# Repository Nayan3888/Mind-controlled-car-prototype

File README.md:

# 🧠🚗 Mind-Controlled Car using EEG and IoT

A smart **EEG-based Mind-Controlled Car** system that uses the **NeuroSky MindWave Mobile 2** headset to interpret brainwave signals and control an **ESP32-based robot car** via Bluetooth and HTTP protocols. The system also includes **manual control options** using IR remotes and physical buttons, making it a hybrid multi-input system.

---

## 🚀 Project Overview

This project demonstrates how **EEG (Electroencephalography) signals** can be used to control a robotic vehicle. The headset detects **attention, meditation, and blinks**, which are processed in a **Flutter app** to make real-time movement decisions. The car is then controlled via **Wi-Fi (ESP32 HTTP)** based on the detected mental commands.

---

## 🧩 Features

* 🔗 **Real-time EEG signal processing** from NeuroSky MindWave
* 📱 **Flutter mobile app** for Bluetooth communication and UI
* 🌐 **Wi-Fi-based car control** using ESP32 (HTTP GET/POST)
* 👀 **Blink detection** to trigger left/right movement
* 🧘 **Meditation level** to control reverse
* 🚘 Manual controls via:

  * 📡 IR Remote
  * 🔘 Push buttons on PCB
* 📈 Real-time brainwave data graph (Alpha, Beta, Gamma, etc.)
* 🔌 Power-efficient and multi-mode operation

---

## 🛠️ Hardware Components

| Component               | Description                     |
| ----------------------- | ------------------------------- |
| 🧠 NeuroSky MindWave    | EEG Headset                     |
| 🔲 ESP32-WROOM-32       | Microcontroller with Wi-Fi      |
| 📱 Android Phone        | For Flutter App and EEG parsing |
| 🛞 L298N Motor Driver   | For dual DC motor control       |
| 🔋 Battery              | For powering motors and board   |
| 🔘 IR Receiver + Remote | Manual car control              |
| 📟 16x2 I2C LCD         | (Optional) Display EEG/Status   |
| 💧 Moisture/pH Sensor   | (Optional extension)            |

---

## 📲 Flutter App Features

* Scan and connect to MindWave EEG device (BLE)
* Graphically display EEG metrics (attention, meditation, blink strength)
* Send movement commands to ESP32 via Wi-Fi
* Real-time feedback and alerts

---

## 🔧 How It Works

1. MindWave reads brain signals.
2. Flutter app parses EEG data over Bluetooth using `flutter_blue_plus`.
3. Based on blink or meditation thresholds:

   * Sends commands (e.g., `FORWARD`, `LEFT`, `REVERSE`) to ESP32 via HTTP.
4. ESP32 receives the command and sets motor pins HIGH/LOW using L298N.
5. Manual override is always available via IR or push buttons.

---

## 🧠 EEG Signal Mapping

| EEG Input      | Action Triggered   |
| -------------- | ------------------ |
| Blink Detected | Turn Left or Right |
| Meditation > X | Move in Reverse    |
| Attention > Y  | Move Forward       |
| Idle           | Stop               |

---

## 🔌 Pin Configuration (ESP32)

| Pin      | Description      |
| -------- | ---------------- |
| D5, D18  | Motor A (Front)  |
| D19, D21 | Motor B (Back)   |
| D22      | IR Sensor        |
| D23      | Button 1 (Left)  |
| D25      | Button 2 (Right) |
| 3V3, GND | Power Rails      |

---

## 📁 Project Structure

```
MindControlledCar/
├── flutter_app/           # EEG data processing & UI
├── esp32_code/            # Arduino code for ESP32
├── pcb_design/            # KiCad schematic & PCB layout
├── images/                # System architecture, demo screenshots
└── README.md              # Project documentation
```

---

## 📷 Demo

---

## 📦 Future Enhancements

* Voice commands as secondary control
* Real-time location tracking using GPS
* Web dashboard with EEG logs
* Adaptive control with ML-based pattern recognition

---

## 🤝 Credits

* **Developed by:** Nayan Parekh ,Ved Patel
* **EEG Hardware:** NeuroSky MindWave Mobile 2
* **Embedded System:** ESP32
* **Mobile App:** Flutter

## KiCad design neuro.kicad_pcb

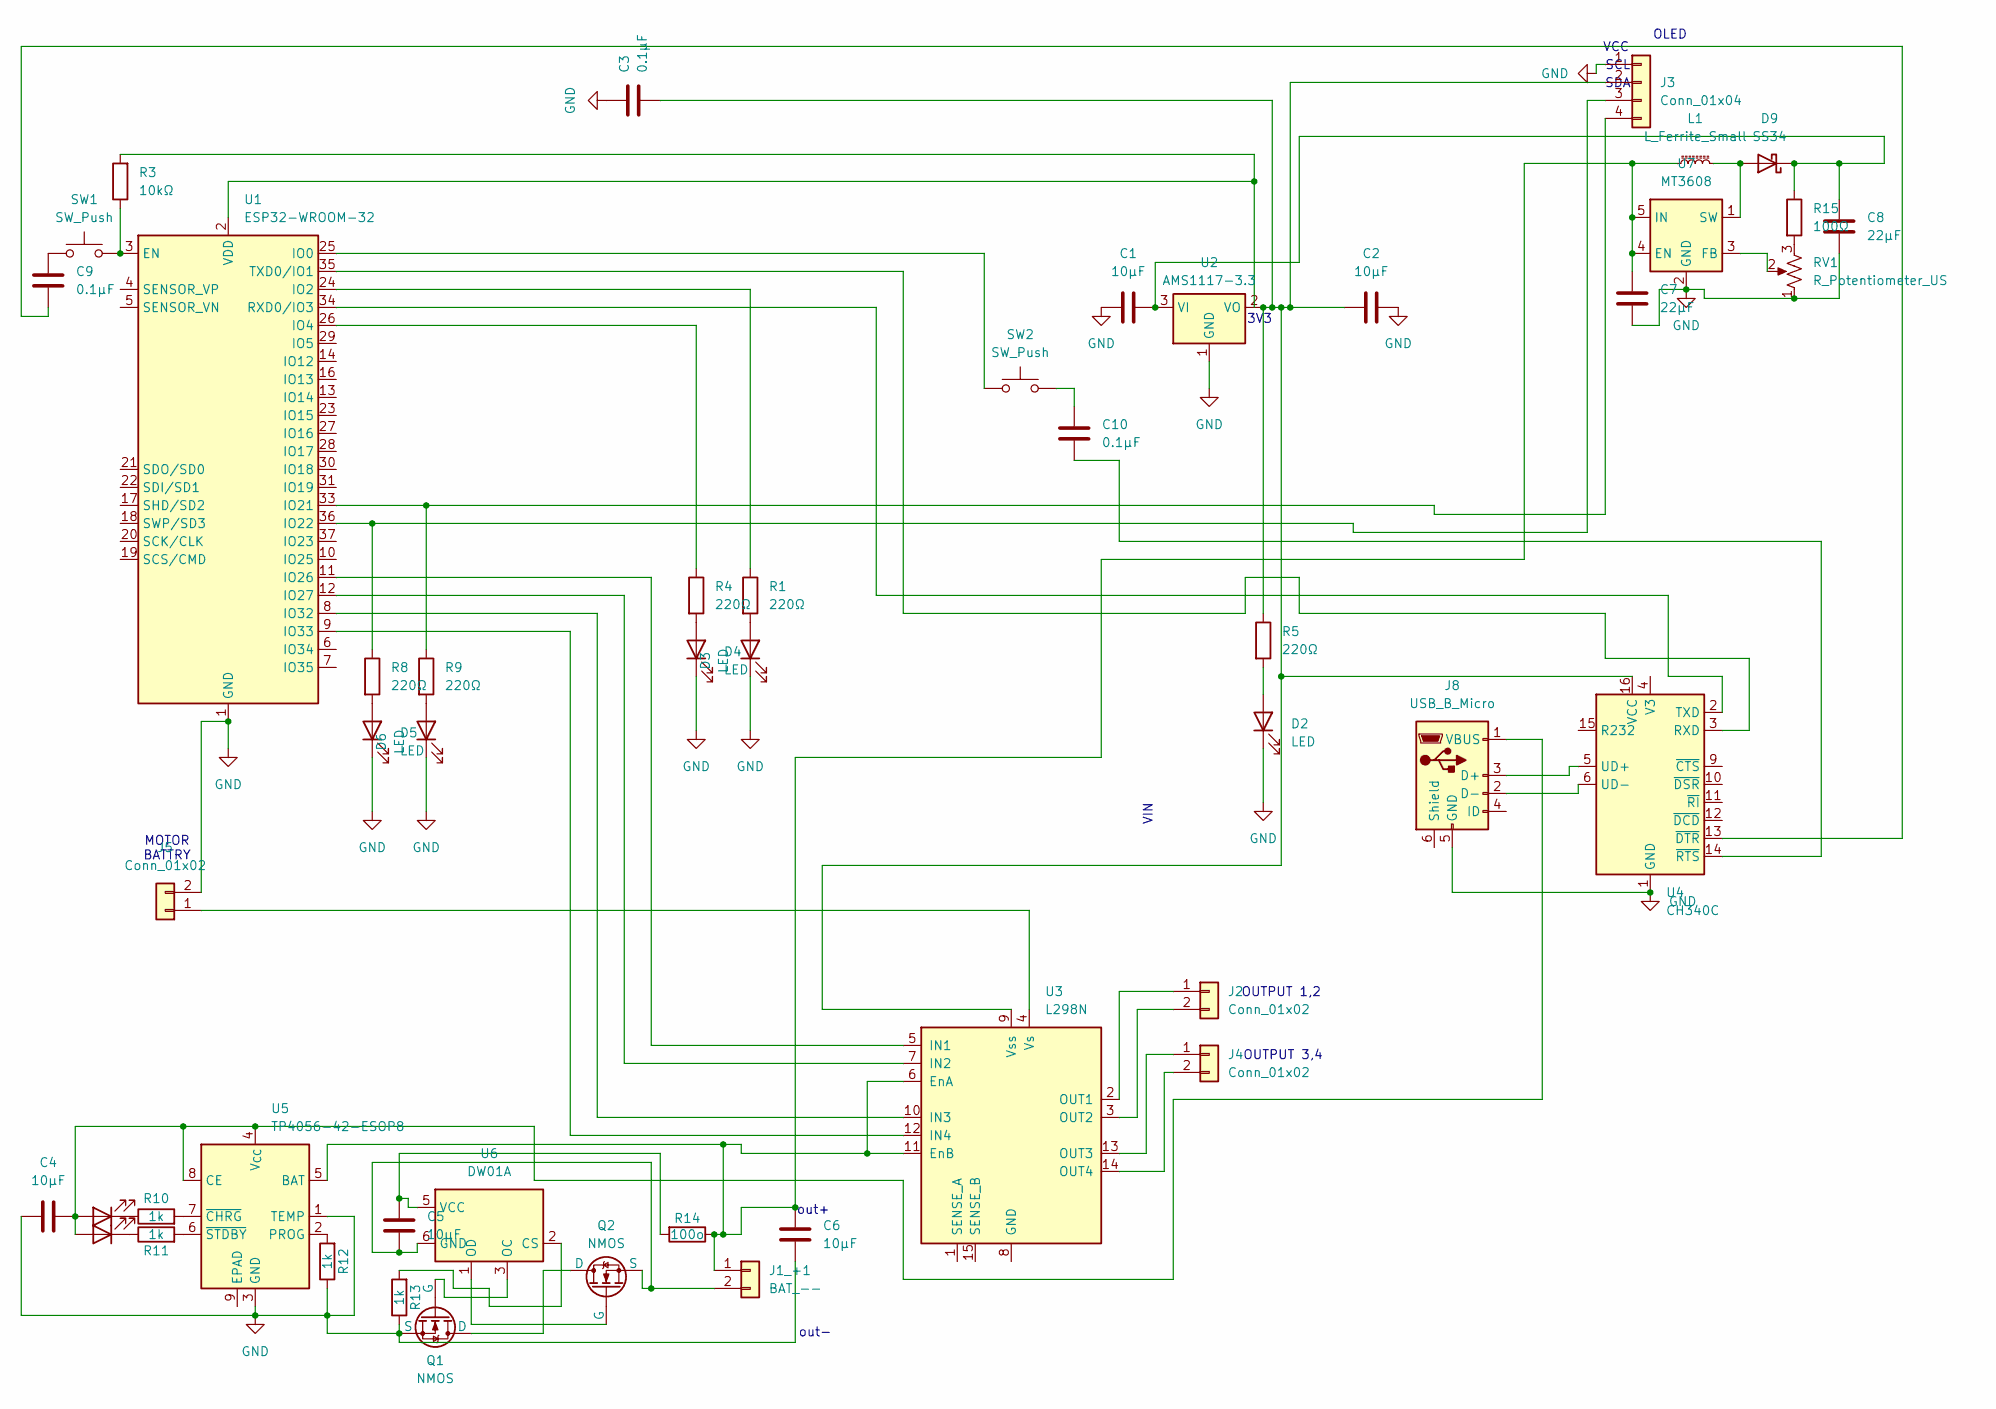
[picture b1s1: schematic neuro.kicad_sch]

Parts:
C1, C2, C4, C5, C6: 10µF; C_1206_3216Metric
C3, C9, C10: 0.1µF; C_1206_3216Metric
C7, C8: 22µF; C_1206_3216Metric
D2, D3, D4, D5, D6, D7, D8: LED; LED_0603_1608Metric
D9: SS34; D_SMA
J1_+1: BAT_--; JST_EH_S2B-EH_1x02_P2.50mm_Horizontal
J2, J4, J5: Conn_01x02; JST_EH_S2B-EH_1x02_P2.50mm_Horizontal
J3: Conn_01x04; JST_EH_S4B-EH_1x04_P2.50mm_Horizontal
J8: USB_B_Micro; USB_Micro-B_Amphenol_10103594-0001LF_Horizontal
L1: L_Ferrite_Small; L_1210_3225Metric
Q1, Q2: NMOS; SOT-23
R1, R4, R5, R8, R9: 220Ω; R_0603_1608Metric
R3: 10kΩ; R_0603_1608Metric
R10, R11, R12, R13: 1k; R_0603_1608Metric
R14: 100o; R_0603_1608Metric
R15: 100Ω; R_0603_1608Metric
RV1: R_Potentiometer_US; Potentiometer_Bourns_3296Y_Vertical
SW1, SW2: SW_Push; SW_SPST_EVQP7C
U1: ESP32-WROOM-32
U2: AMS1117-3.3; SOT-223
U3: L298N; TO-220-15_P2.54x5.08mm_StaggerEven_Lead4.58mm_Vertical
U4: CH340C; SOIC-16_3.9x9.9mm_P1.27mm
U5: TP4056-42-ESOP8; SOIC-8-1EP_3.9x4.9mm_P1.27mm_EP2.41x3.3mm_ThermalVias
U6: DW01A; SOT-23-6
U7: MT3608; SOT-23-6

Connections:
GND: C1.1, C2.2, C3.1, C4.1, C6.1, C7.1, C8.1, D2.1 (K), D3.1 (K), D4.1 (K), D5.1 (K), D6.1 (K), J3.1, J5.2, J8.5 (GND), Q1.3 (S), R12.1, R13.1, RV1.1, U1.1 (GND), U1.15 (GND), U1.38 (GND), U1.39 (GND), U2.1 (GND), U4.1 (GND), U5.1 (TEMP), U5.3 (GND), U7.2 (GND)
unnamed: C9.2, SW1.1
unnamed: C10.2, SW2.2
unnamed: D2.2 (A), R5.2
unnamed: D3.2 (A), R1.2
unnamed: D4.2 (A), R4.2
unnamed: D5.2 (A), R8.2
unnamed: D6.2 (A), R9.2
unnamed: C4.2, D7.2 (A), D8.2 (A), J8.1 (VBUS), U5.4 (V_{CC}), U5.8 (CE)
unnamed: D7.1 (K), R10.1
unnamed: D8.1 (K), R11.1
unnamed: D9.2 (A), L1.2, U7.1 (SW)
unnamed: C1.2, C8.2, D9.1 (K), R15.1, U2.3 (VI)
unnamed: C6.2, C7.2, J1_+1.1, L1.1, R14.1, U3.6 (EnA), U3.11 (EnB), U5.5 (BAT), U7.4 (EN), U7.5 (IN)
unnamed: C5.1, J1_+1.2, Q2.3 (S), U6.6 (GND)
unnamed: J2.1, U3.2 (OUT1)
unnamed: J2.2, U3.3 (OUT2)
unnamed 17: C2.1, C3.2, J3.2, R5.1, U2.2 (VO), U3.9 (Vss), U4.16 (VCC); also elsewhere on the board
unnamed 18: J3.3, R8.1, U1.36 (IO22); also elsewhere on the board
unnamed 19: J3.4, R9.1, U1.33 (IO21); also elsewhere on the board
unnamed: J4.1, U3.13 (OUT3)
unnamed: J4.2, U3.14 (OUT4)
unnamed: J5.1, U3.4 (Vs)
unnamed: J8.3 (D+), U4.5 (UD+)
unnamed: J8.2 (D-), U4.6 (UD-)
unnamed: Q1.1 (D), Q2.1 (D)
unnamed: Q1.2 (G), U6.3 (OC)
unnamed: Q2.2 (G), U6.1 (OD)
unnamed: R15.2, RV1.3
unnamed: R3.1, SW1.2, U1.3 (EN)
unnamed: SW2.1, U1.25 (IO0)
unnamed: R1.1, U1.24 (IO2)
unnamed: R4.1, U1.26 (IO4)
unnamed: U1.11 (IO26), U3.5 (IN1)
unnamed: U1.12 (IO27), U3.7 (IN2)
unnamed: U1.8 (IO32), U3.10 (IN3)
unnamed: U1.9 (IO33), U3.12 (IN4)
unnamed: U1.34 (RXD0/IO3), U4.2 (TXD)
unnamed: U1.35 (TXD0/IO1), U4.3 (RXD)
unnamed: R3.2, U1.2 (VDD)
unnamed: C9.1, U4.13 (~DTR)
unnamed: C10.1, U4.14 (~RTS)
unnamed: R12.2, U5.2 (PROG)
unnamed: R10.2, U5.7 (~CHRG)
unnamed: R11.2, U5.6 (~STDBY)
unnamed: R13.2, U6.2 (CS)
unnamed: C5.2, R14.2, U6.5 (VCC)
unnamed: RV1.2, U7.3 (FB)

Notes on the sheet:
OUTPUT 3,4
MOTOR BATTRY
3V3
SDA
SCL
out+
OUTPUT 1,2
OLED
out-
VCC
VIN

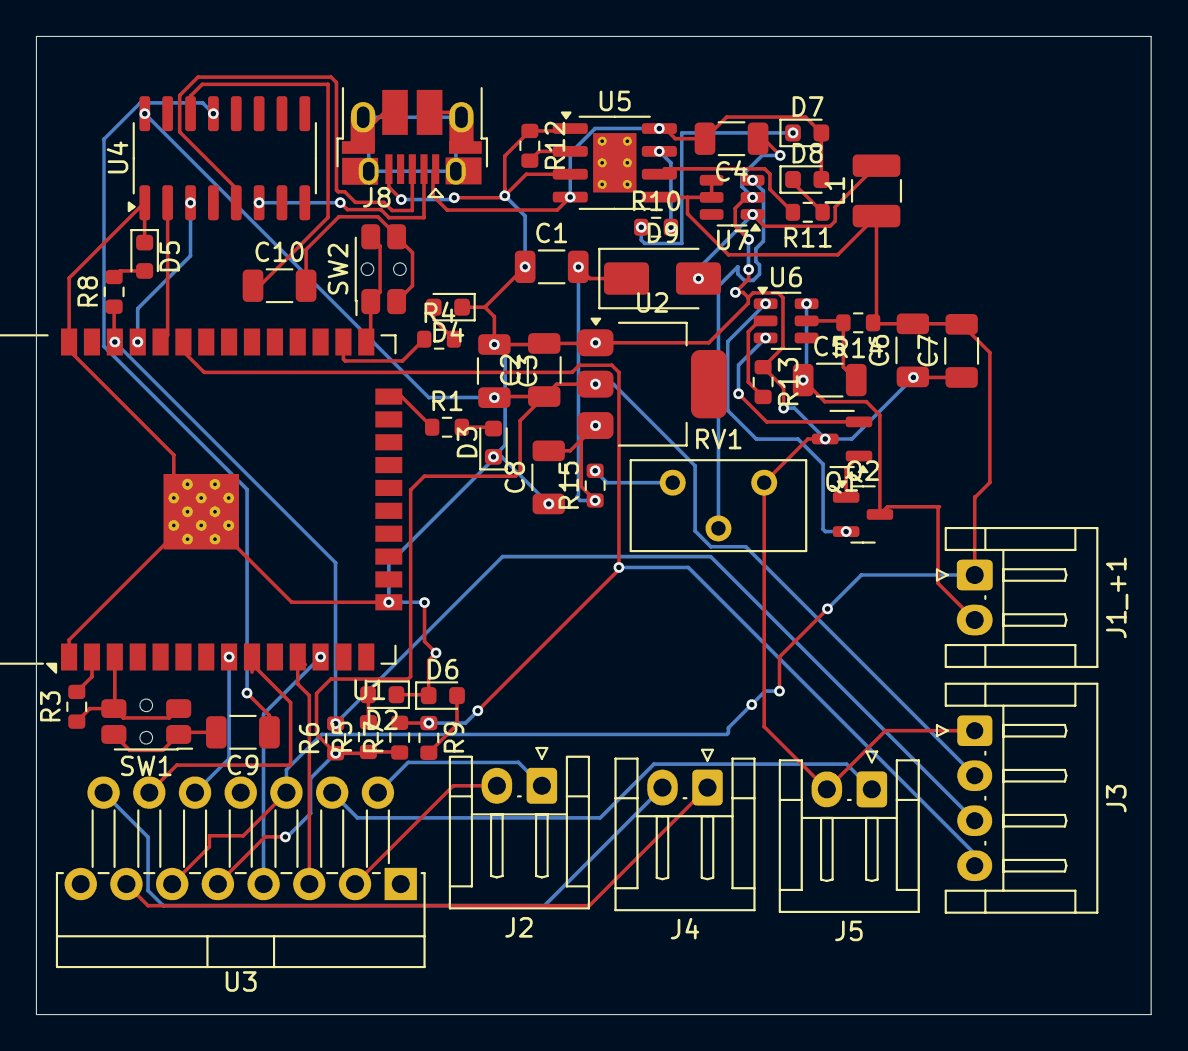
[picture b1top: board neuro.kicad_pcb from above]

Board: 2 copper layers, 61.9 x 54.3 mm, 51 parts (0 on the bottom side), 48 nets.

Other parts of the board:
R6, R7: 10kΩ; R_0603_1608Metric

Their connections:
unnamed 17: R6.1, R7.1; also elsewhere on the board
unnamed 18: R6.2; also elsewhere on the board
unnamed 19: R7.2; also elsewhere on the board

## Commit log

2025-07-08 Create esp32
